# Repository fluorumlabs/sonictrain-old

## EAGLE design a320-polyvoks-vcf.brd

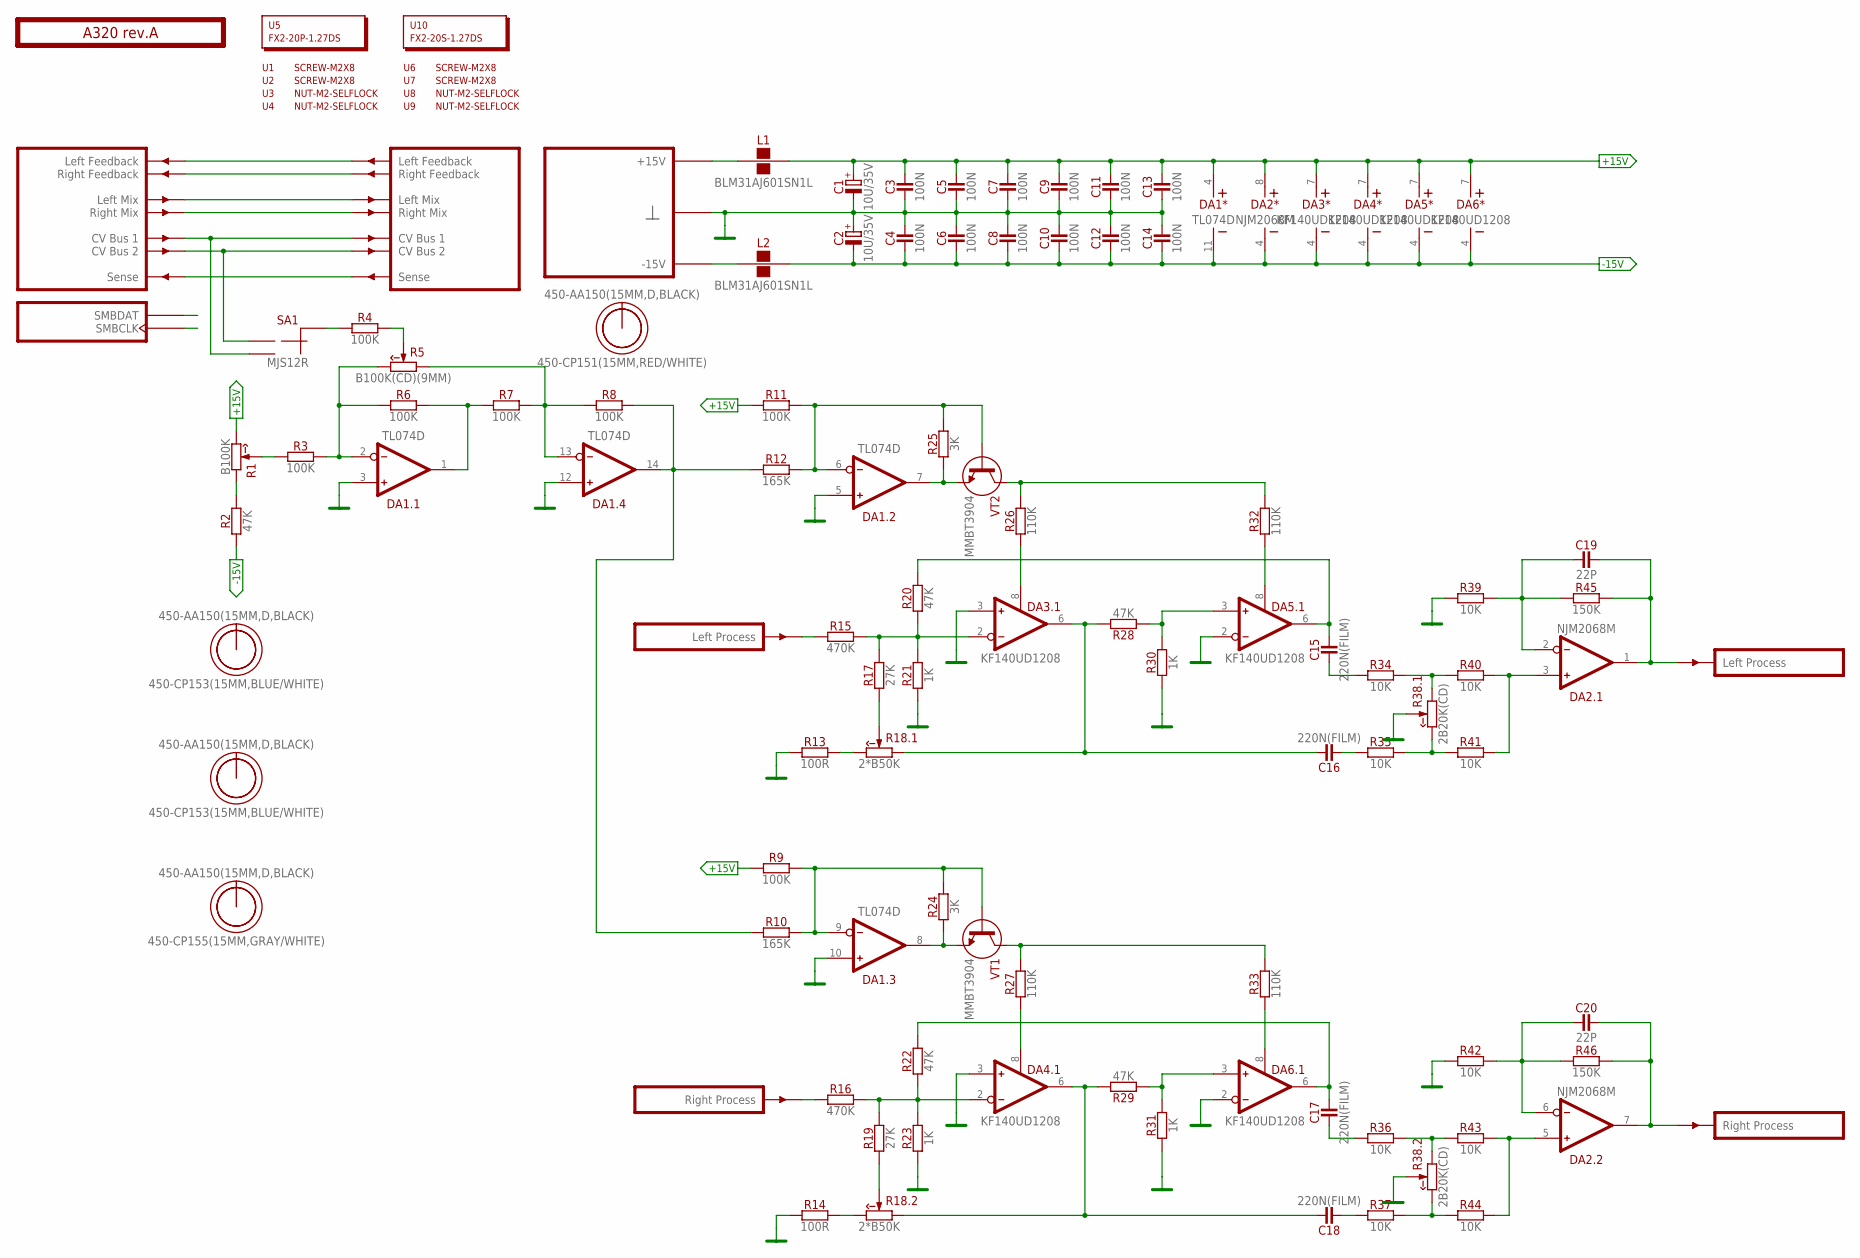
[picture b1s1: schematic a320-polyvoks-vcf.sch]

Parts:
C1, C2: 10U/35V; E2-5
C3, C4, C5, C6, C7, C8, C9, C10, C11, C12, C13, C14: 100N; C-0805
C15, C16, C17, C18: 220N(FILM); C050-025X075
C19, C20: 22P; C-0805
DA1: TL074D; SO-14
DA2: NJM2068M; SO-8
DA3, DA4, DA5, DA6: KF140UD1208; SO-8
L1, L2: BLM31AJ601SN1L; 1206
O1, O3, O5, O7: 450-AA150(15MM,D,BLACK); EMPTY
O2, O4: 450-CP153(15MM,BLUE/WHITE); EMPTY
O6: 450-CP155(15MM,GRAY/WHITE); EMPTY
O8: 450-CP151(15MM,RED/WHITE); EMPTY
PCB1: A320 rev.A; ST2-BOARD-50
R1: B100K; RV11-SINGLE
R2, R20, R22, R28, R29: 47K; R-0805
R3, R4, R6, R7, R8, R9, R11: 100K; R-0805
R5: B100K(CD)(9MM); RV09-SINGLE
R10, R12: 165K; R-0805
R13, R14: 100R; R-0805
R15, R16: 470K; R-0805
R17, R19: 27K; R-0805
R18: 2*B50K; RV11-DUAL
R21, R23, R30, R31: 1K; R-0805
R24, R25: 3K; R-0805
R26, R27, R32, R33: 110K; R-0805
R34, R35, R36, R37, R39, R40, R41, R42, R43, R44: 10K; R-0805
R38: 2B20K(CD); RV11-DUAL
R45, R46: 150K; R-0805
SA1: MJS12R; APEM-MJS12R
U1, U2, U6, U7: SCREW-M2X8; EMPTY
U3, U4, U8, U9: NUT-M2-SELFLOCK; EMPTY
U5: FX2-20P-1.27DS; EMPTY
U10: FX2-20S-1.27DS; EMPTY
VT1, VT2: MMBT3904; SOT23

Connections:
+15V: C1.+, C3.2, C5.2, C7.2, C9.2, C11.2, C13.2, DA1.4 (V+), DA2.8 (V+), DA3.7 (V+), DA4.7 (V+), DA5.7 (V+), DA6.7 (V+), L1.2, R1.3 (CW), R9.1, R11.1
-15V: C2.-, C4.1, C6.1, C8.1, C10.1, C12.1, C14.1, DA1.11 (V-), DA2.4 (V-), DA3.4 (V-), DA4.4 (V-), DA5.4 (V-), DA6.4 (V-), L2.2, R2.1
GND: C1.-, C2.+, C3.1, C4.2, C5.1, C6.2, C7.1, C8.2, C9.1, C10.2, C11.1, C12.2, C13.1, C14.2, DA1.3 (IN+), DA1.5 (IN+), DA1.10 (IN+), DA1.12 (IN+), DA3.3 (IN+), DA4.3 (IN+), DA5.2 (IN-), DA6.2 (IN-), PCB1.B4 (GND), PCB1.B4' (GND), PCB1.B5 (GND), PCB1.B5' (GND), PCB1.B6 (GND), PCB1.B6' (GND), PCB1.B7 (GND), PCB1.B7' (GND), PCB1.B8 (GND), PCB1.B8' (GND), R13.1, R14.1, R21.1, R23.1, R30.1, R31.1, R38.2 (W), R38.2' (W), R39.1, R42.1
LMIX: PCB1.ALMIX (LMIX), PCB1.ALMIX' (LMIX')
unnamed: L1.1, PCB1.A+15 (P+15V), PCB1.A+15' (P+15V), PCB1.B+15 (P+15V), PCB1.B+15' (P+15V)
unnamed: PCB1.ALFBK (LFBK), PCB1.ALFBK' (LFBK')
unnamed: R4.2, R5.2 (W)
unnamed: PCB1.ARFBK (RFBK), PCB1.ARFBK' (RFBK')
unnamed: DA1.2 (IN-), R3.2, R5.3 (CW), R6.1
unnamed: DA1.1 (OUT), R6.2, R7.1
unnamed: DA1.13 (IN-), R5.1 (CCW), R7.2, R8.1
unnamed: R1.1 (CCW), R2.2
unnamed: R4.1, SA1.C (CM)
unnamed: R34.2, R38.1 (CCW), R40.1
unnamed: DA1.9 (IN-), R9.2, R10.2, R24.2, VT1.1 (B)
unnamed: DA1.6 (IN-), R11.2, R12.2, R25.2, VT2.1 (B)
unnamed: R1.2 (W), R3.1
unnamed: DA1.8 (OUT), R24.1, VT1.2 (E)
unnamed: PCB1.ACV1 (CV1), PCB1.ACV1' (CV1'), SA1.NO (2)
unnamed: PCB1.BSENSE (SENSE), PCB1.BSENSE' (SENSE')
unnamed: DA1.7 (OUT), R25.1, VT2.2 (E)
unnamed: DA2.3 (IN+), R40.2, R41.2
unnamed: R36.2, R38.1' (CCW), R43.1
unnamed: C19.2, DA2.1 (OUT), PCB1.BOUTL' (OUTL), R45.2
unnamed: C20.1, DA2.6 (IN-), R42.2, R46.1
unnamed: DA3.2 (IN-), R15.2, R17.2, R20.1, R21.2
unnamed: C16.2, DA3.6 (OUT), R18.1 (CCW), R28.2
unnamed: DA5.3 (IN+), R28.1, R30.2
unnamed: L2.1, PCB1.A-15 (P-15V), PCB1.A-15' (P-15V), PCB1.B-15 (P-15V), PCB1.B-15' (P-15V)
unnamed: DA3.8 (ISET), R26.1
unnamed: C15.2, DA5.6 (OUT), R20.2
unnamed: DA1.14 (OUT), R8.2, R10.1, R12.1
unnamed: R13.2, R18.3 (CW)
unnamed: R17.1, R18.2 (W)
unnamed: DA5.8 (ISET), R32.1
unnamed: R26.2, R32.2, VT2.3 (C)
unnamed: C15.1, R34.1
unnamed: C16.1, R35.1
unnamed: DA2.5 (IN+), R43.2, R44.2
unnamed: R37.2, R38.3' (CW), R44.1
unnamed: C20.2, DA2.7 (OUT), PCB1.BOUTR' (OUTR), R46.2
unnamed: PCB1.ASMBDAT (SMBDAT), PCB1.ASMBDAT' (SMBDAT)
unnamed: DA4.2 (IN-), R16.2, R19.2, R22.1, R23.2
unnamed: C18.2, DA4.6 (OUT), R18.1' (CCW), R29.2
unnamed: DA6.3 (IN+), R29.1, R31.2
unnamed: PCB1.ACV2 (CV2), PCB1.ACV2' (CV2'), SA1.NC (1)
unnamed: PCB1.ASMBCLK (SMBCLK), PCB1.ASMBCLK' (SMBCLK)
unnamed: C17.2, DA6.6 (OUT), R22.2
unnamed: R14.2, R18.3' (CW)
unnamed: R18.2' (W), R19.1
unnamed: DA4.8 (ISET), R27.1
unnamed: DA6.8 (ISET), R33.1
unnamed: R27.2, R33.2, VT1.3 (C)
unnamed: R35.2, R38.3 (CW), R41.1
unnamed: C17.1, R36.1
unnamed: C18.1, R37.1
unnamed: PCB1.BINL (INL), R15.1
unnamed: PCB1.BINR (INR), R16.1
unnamed: C19.1, DA2.2 (IN-), R39.2, R45.1
RMIX: PCB1.ARMIX (RMIX), PCB1.ARMIX' (RMIX')

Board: 2 copper layers, 96 parts (0 on the bottom side), 60 nets, no tracks yet.

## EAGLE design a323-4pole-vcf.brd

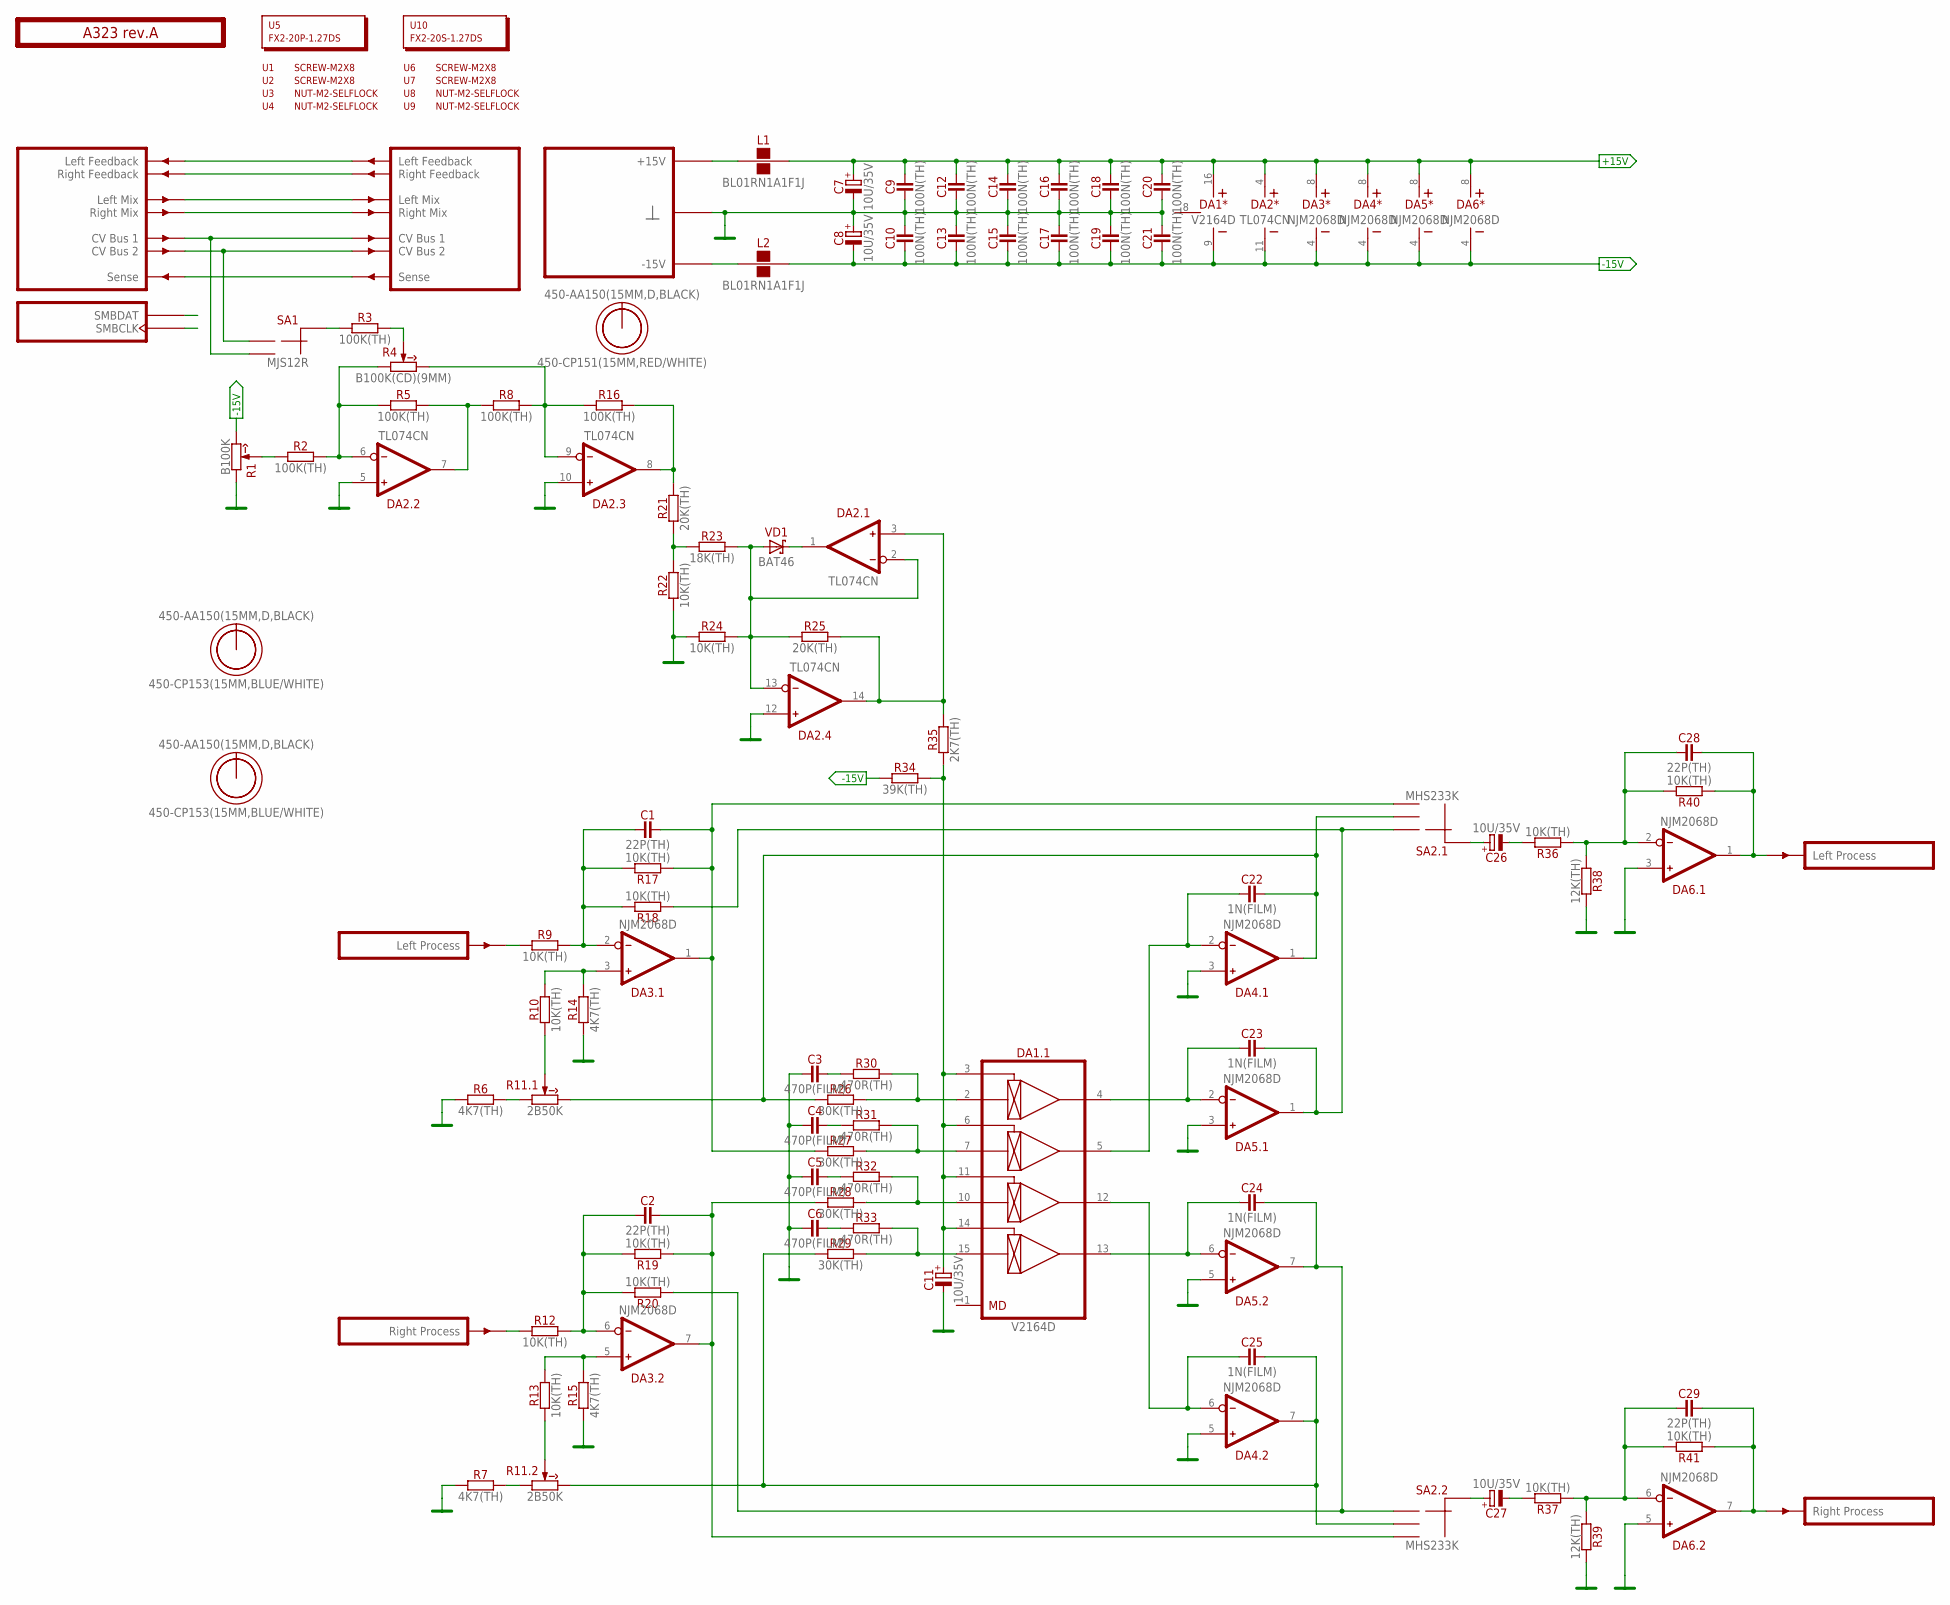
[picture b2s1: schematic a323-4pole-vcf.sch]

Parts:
C1, C2, C28, C29: 22P(TH); C050-024X044
C3, C4, C5, C6: 470P(FILM); C050-055X075
C7, C8, C11, C26, C27: 10U/35V; E2-5
C9, C10, C12, C13, C14, C15, C16, C17, C18, C19, C20, C21: 100N(TH); C050-024X044
C22, C23, C24, C25: 1N(FILM); C050-025X075
DA1: V2164D; DIP-16
DA2: TL074CN; DIP-14
DA3, DA4, DA5, DA6: NJM2068D; DIP-8
L1, L2: BL01RN1A1F1J; BL01RN1A
O1, O3, O5: 450-AA150(15MM,D,BLACK); EMPTY
O2, O4: 450-CP153(15MM,BLUE/WHITE); EMPTY
O6: 450-CP151(15MM,RED/WHITE); EMPTY
PCB1: A323 rev.A; ST2-BOARD-74
R1: B100K; RV11-SINGLE
R2, R3, R5, R8, R16: 100K(TH); R-0207/10
R4: B100K(CD)(9MM); RV09-SINGLE
R6, R7, R14, R15: 4K7(TH); R-0207/10
R9, R10, R12, R13, R17, R18, R19, R20, R22, R24, R36, R37, R40, R41: 10K(TH); R-0207/10
R11: 2B50K; RV11-DUAL
R21, R25: 20K(TH); R-0207/10
R23: 18K(TH); R-0207/10
R26, R27, R28, R29: 30K(TH); R-0207/10
R30, R31, R32, R33: 470R(TH); R-0207/10
R34: 39K(TH); R-0207/10
R35: 2K7(TH); R-0207/10
R38, R39: 12K(TH); R-0207/10
SA1: MJS12R; APEM-MJS12R
SA2: MHS233K; APEM-MHS233K
U1, U2, U6, U7: SCREW-M2X8; EMPTY
U3, U4, U8, U9: NUT-M2-SELFLOCK; EMPTY
U5: FX2-20P-1.27DS; EMPTY
U10: FX2-20S-1.27DS; EMPTY
VD1: BAT46; DO35-7

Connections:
+15V: C7.+, C9.2, C12.2, C14.2, C16.2, C18.2, C20.2, DA1.16 (V+), DA2.4 (V+), DA3.8 (V+), DA4.8 (V+), DA5.8 (V+), DA6.8 (V+), L1.2
-15V: C8.-, C10.1, C13.1, C15.1, C17.1, C19.1, C21.1, DA1.9 (V-), DA2.11 (V-), DA3.4 (V-), DA4.4 (V-), DA5.4 (V-), DA6.4 (V-), L2.2, R1.3 (CW), R34.1
GND: C3.1, C4.1, C5.1, C6.1, C7.-, C8.+, C9.1, C10.2, C11.-, C12.1, C13.2, C14.1, C15.2, C16.1, C17.2, C18.1, C19.2, C20.1, C21.2, DA1.8 (GND), DA2.5 (IN+), DA2.10 (IN+), DA2.12 (IN+), DA4.3 (IN+), DA4.5 (IN+), DA5.3 (IN+), DA5.5 (IN+), DA6.3 (IN+), DA6.5 (IN+), PCB1.B4 (GND), PCB1.B4' (GND), PCB1.B5 (GND), PCB1.B5' (GND), PCB1.B6 (GND), PCB1.B6' (GND), PCB1.B7 (GND), PCB1.B7' (GND), PCB1.B8 (GND), PCB1.B8' (GND), R1.1 (CCW), R6.2, R7.2, R14.1, R15.1, R22.1, R24.1, R38.2, R39.2
LMIX: PCB1.ALMIX (LMIX), PCB1.ALMIX' (LMIX')
unnamed: L1.1, PCB1.A+15 (P+15V), PCB1.A+15' (P+15V), PCB1.B+15 (P+15V), PCB1.B+15' (P+15V)
unnamed: PCB1.ALFBK (LFBK), PCB1.ALFBK' (LFBK')
unnamed: R3.2, R4.2 (W)
unnamed: PCB1.ARFBK (RFBK), PCB1.ARFBK' (RFBK')
unnamed: DA2.6 (IN-), R2.2, R4.1 (CCW), R5.1
unnamed: DA2.7 (OUT), R5.2, R8.1
unnamed: DA2.9 (IN-), R4.3 (CW), R8.2, R16.1
unnamed: C2.1, DA3.6 (IN-), R12.2, R19.2, R20.2
unnamed: R3.1, SA1.C (CM)
unnamed: C1.1, DA3.2 (IN-), R9.2, R17.2, R18.2
unnamed: DA3.3 (IN+), R10.2, R14.2
unnamed: R10.1, R11.2 (W)
unnamed: R1.2 (W), R2.1
unnamed: R6.1, R11.1 (CCW)
unnamed: PCB1.ACV1 (CV1), PCB1.ACV1' (CV1'), SA1.NO (2)
unnamed: PCB1.BSENSE (SENSE), PCB1.BSENSE' (SENSE')
unnamed: R21.1, R22.2, R23.1
unnamed: DA1.2 (IN1), R26.2, R30.2
unnamed: C1.2, DA3.1 (OUT), R17.1, R27.1, SA2.3
unnamed: DA1.7 (IN2), R27.2, R31.2
unnamed: DA1.10 (IN3), R28.2, R32.2
unnamed: DA1.15 (IN4), R29.2, R33.2
unnamed: C3.2, R30.1
unnamed: C4.2, R31.1
unnamed: L2.1, PCB1.A-15 (P-15V), PCB1.A-15' (P-15V), PCB1.B-15 (P-15V), PCB1.B-15' (P-15V)
unnamed: C5.2, R32.1
unnamed: C6.2, R33.1
unnamed: DA2.8 (OUT), R16.2, R21.2
unnamed: DA3.5 (IN+), R13.2, R15.2
unnamed: R11.2' (W), R13.1
unnamed: R7.1, R11.1' (CCW)
unnamed: C26.+, SA2.CMN (CM)
unnamed: C2.2, DA3.7 (OUT), R19.1, R28.1, SA2.3' (3)
unnamed: C22.1, DA1.5 (OUT2), DA4.2 (IN-)
unnamed: C22.2, DA4.1 (OUT), R11.3 (CW), R26.1, SA2.2
unnamed: C23.1, DA1.4 (OUT1), DA5.2 (IN-)
unnamed: C23.2, DA5.1 (OUT), R18.1, SA2.1
unnamed: PCB1.ASMBDAT (SMBDAT), PCB1.ASMBDAT' (SMBDAT)
unnamed: C24.1, DA1.13 (OUT4), DA5.6 (IN-)
unnamed: C24.2, DA5.7 (OUT), R20.1, SA2.1' (1)
unnamed: C25.1, DA1.12 (OUT3), DA4.6 (IN-)
unnamed: PCB1.ACV2 (CV2), PCB1.ACV2' (CV2'), SA1.NC (1)
unnamed: PCB1.ASMBCLK (SMBCLK), PCB1.ASMBCLK' (SMBCLK)
unnamed: C25.2, DA4.7 (OUT), R11.3' (CW), R29.1, SA2.2' (2)
unnamed: C26.-, R36.2
unnamed: C28.1, DA6.2 (IN-), R36.1, R38.1, R40.2
unnamed: PCB1.BINL (INL), R9.1
unnamed: C28.2, DA6.1 (OUT), PCB1.BOUTL' (OUTL), R40.1
unnamed: C27.+, SA2.CMN' (CM)
unnamed: C27.-, R37.2
unnamed: C29.1, DA6.6 (IN-), R37.1, R39.1, R41.2
unnamed: C29.2, DA6.7 (OUT), PCB1.BOUTR' (OUTR), R41.1
unnamed: DA2.1 (OUT), VD1.C
unnamed: DA2.3 (IN+), DA2.14 (OUT), R25.2, R35.2
unnamed: DA2.2 (IN-), DA2.13 (IN-), R23.2, R24.2, R25.1, VD1.A
unnamed: PCB1.BINR (INR), R12.1
unnamed: C11.+, DA1.3 (CV1), DA1.6 (CV2), DA1.11 (CV3), DA1.14 (CV4), R34.2, R35.1
RMIX: PCB1.ARMIX (RMIX), PCB1.ARMIX' (RMIX')

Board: 2 copper layers, 98 parts (0 on the bottom side), 62 nets, no tracks yet.

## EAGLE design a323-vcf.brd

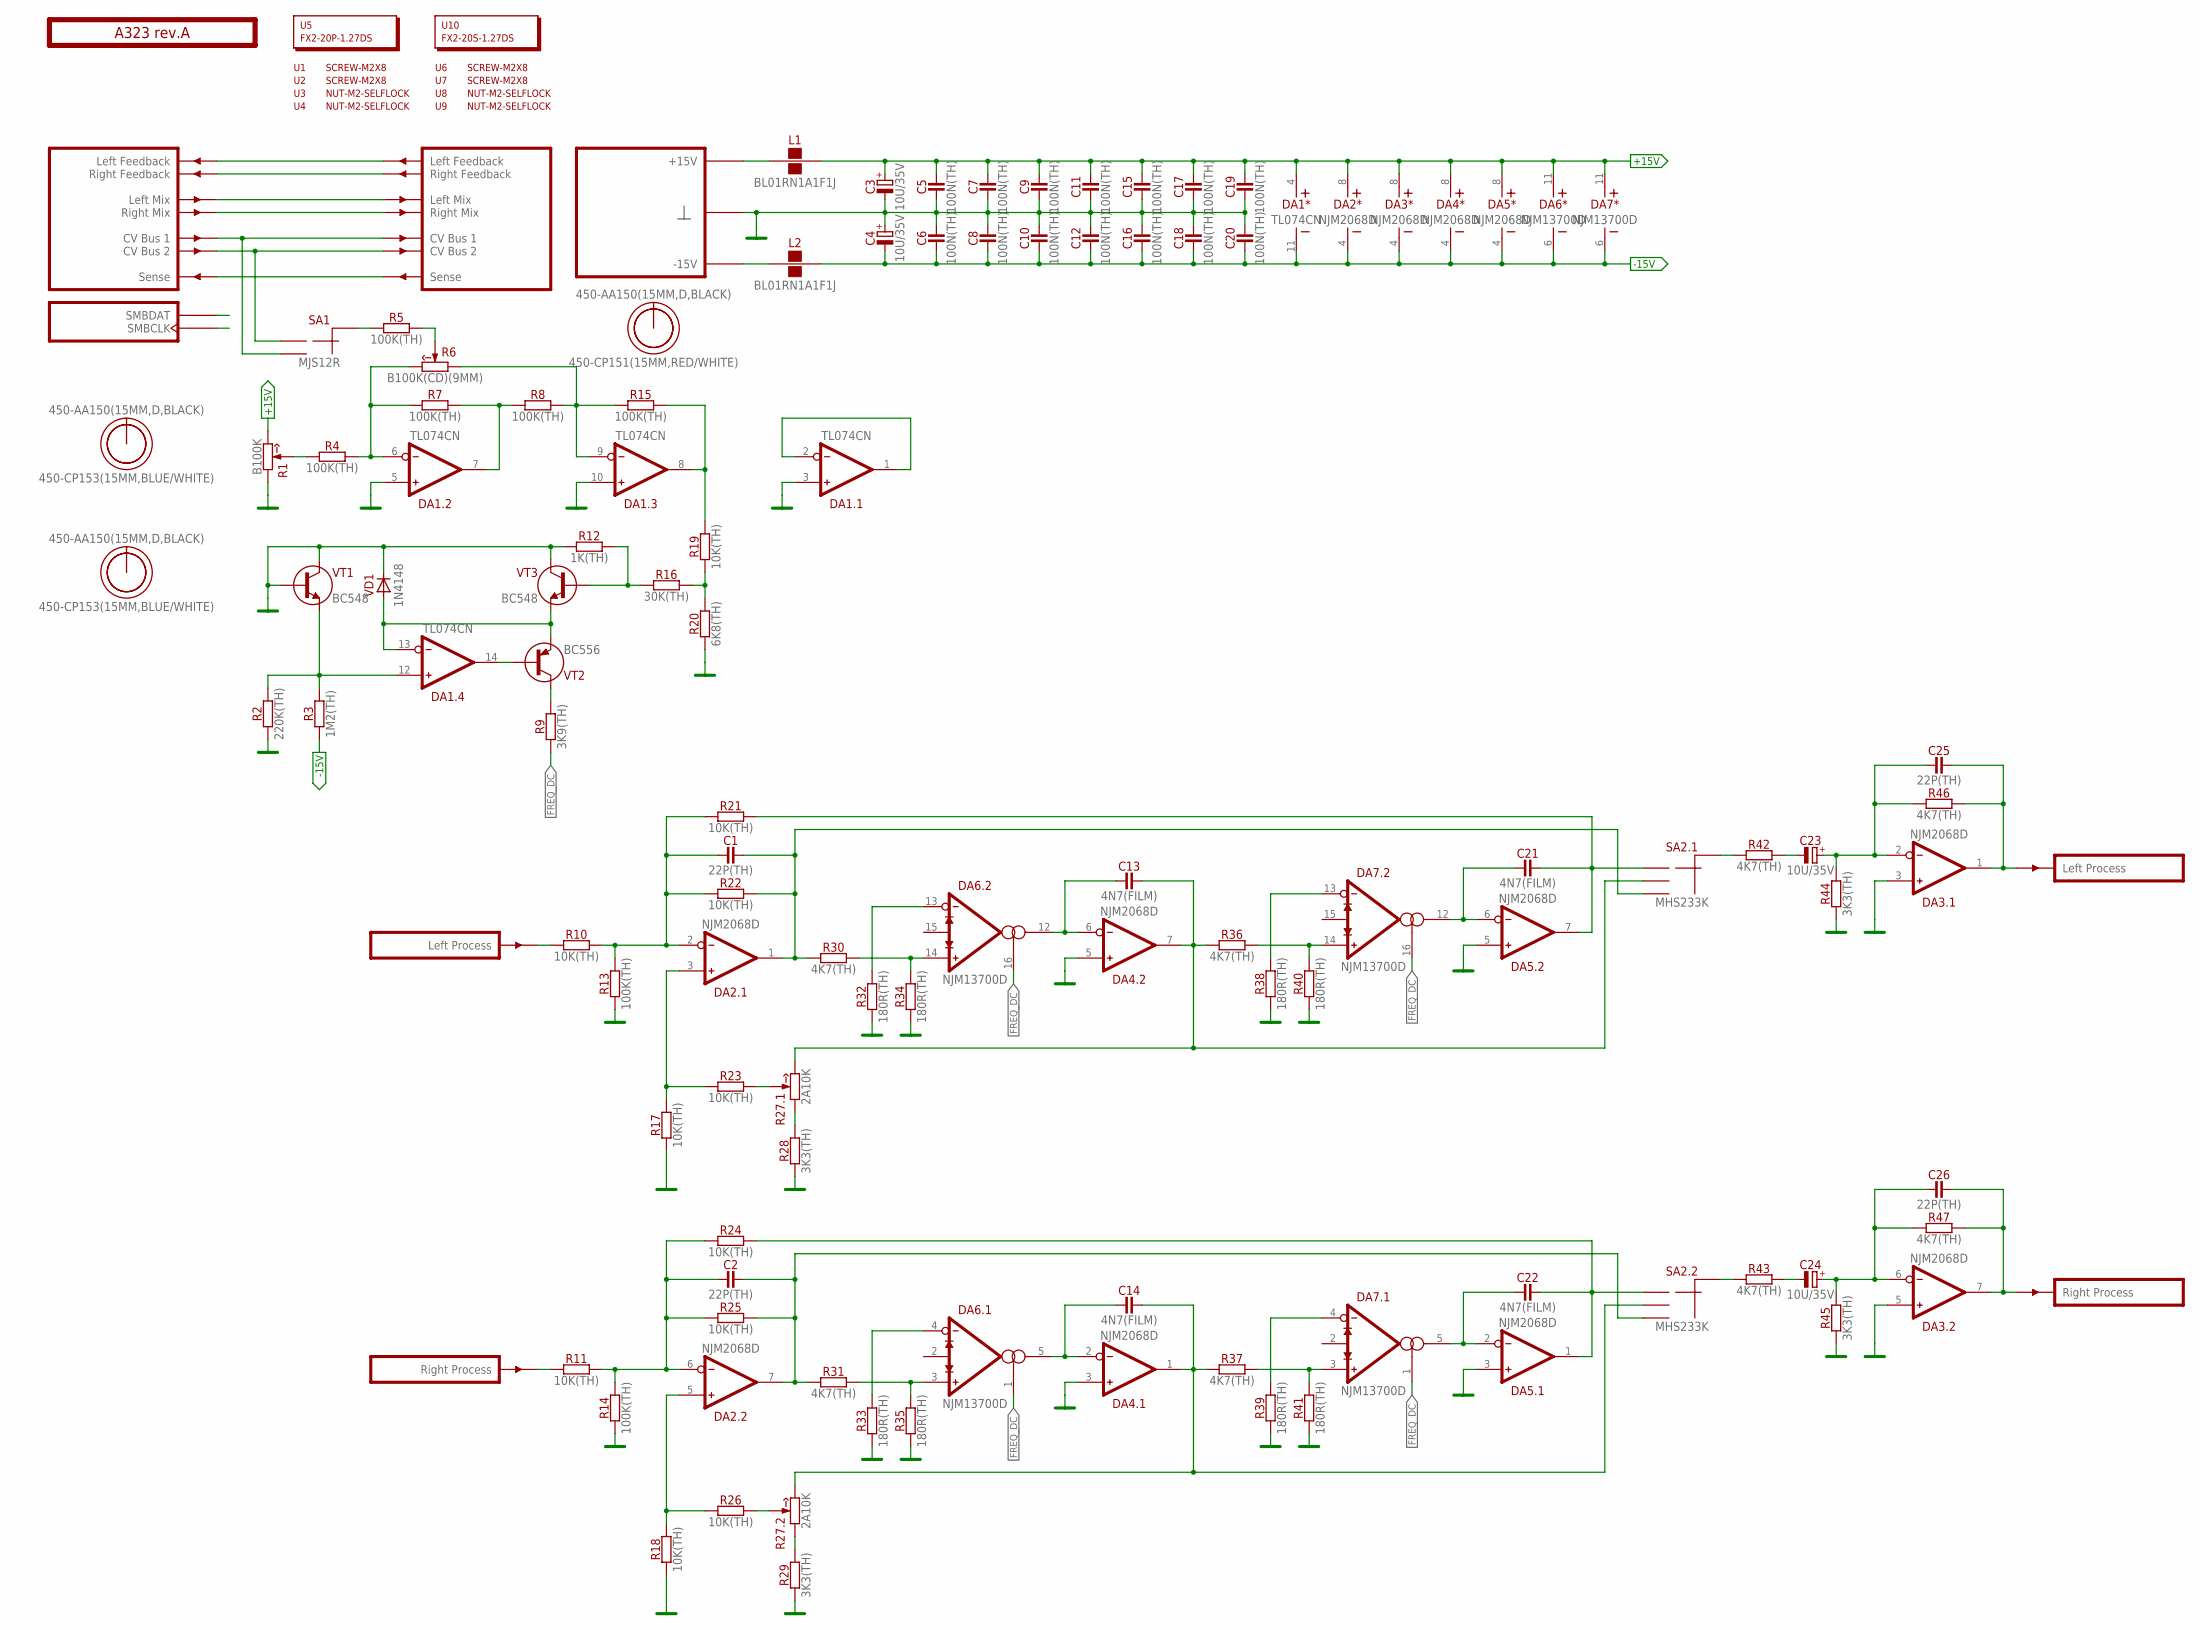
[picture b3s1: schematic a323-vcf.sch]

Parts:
C1, C2, C25, C26: 22P(TH); C050-024X044
C3, C4, C23, C24: 10U/35V; E2-5
C5, C6, C7, C8, C9, C10, C11, C12, C15, C16, C17, C18, C19, C20: 100N(TH); C050-024X044
C13, C14, C21, C22: 4N7(FILM); C050-025X075
DA1: TL074CN; DIP-14
DA2, DA3, DA4, DA5: NJM2068D; DIP-8
DA6, DA7: NJM13700D; DIP-16
L1, L2: BL01RN1A1F1J; BL01RN1A
O1, O3, O5: 450-AA150(15MM,D,BLACK); EMPTY
O2, O4: 450-CP153(15MM,BLUE/WHITE); EMPTY
O6: 450-CP151(15MM,RED/WHITE); EMPTY
PCB1: A323 rev.A; ST2-BOARD-74
R1: B100K; RV11-SINGLE
R2: 220K(TH); R-0207/10
R3: 1M2(TH); R-0207/10
R4, R5, R7, R8, R13, R14, R15: 100K(TH); R-0207/10
R6: B100K(CD)(9MM); RV09-SINGLE
R9: 3K9(TH); R-0207/10
R10, R11, R17, R18, R19, R21, R22, R23, R24, R25, R26: 10K(TH); R-0207/10
R12: 1K(TH); R-0207/10
R16: 30K(TH); R-0207/10
R20: 6K8(TH); R-0207/10
R27: 2A10K; RV11-DUAL
R28, R29, R44, R45: 3K3(TH); R-0207/10
R30, R31, R36, R37, R42, R43, R46, R47: 4K7(TH); R-0207/10
R32, R33, R34, R35, R38, R39, R40, R41: 180R(TH); R-0207/10
SA1: MJS12R; APEM-MJS12R
SA2: MHS233K; APEM-MHS233K
U1, U2, U6, U7: SCREW-M2X8; EMPTY
U3, U4, U8, U9: NUT-M2-SELFLOCK; EMPTY
U5: FX2-20P-1.27DS; EMPTY
U10: FX2-20S-1.27DS; EMPTY
VD1: 1N4148; DO35-7
VT1, VT3: BC548; TO92
VT2: BC556; TO92

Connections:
+15V: C3.+, C5.2, C7.2, C9.2, C11.2, C15.2, C17.2, C19.2, DA1.4 (V+), DA2.8 (V+), DA3.8 (V+), DA4.8 (V+), DA5.8 (V+), DA6.11 (V+), DA7.11 (V+), L1.2, R1.3 (CW)
-15V: C4.-, C6.1, C8.1, C10.1, C12.1, C16.1, C18.1, C20.1, DA1.11 (V-), DA2.4 (V-), DA3.4 (V-), DA4.4 (V-), DA5.4 (V-), DA6.6 (V-), DA7.6 (V-), L2.2, R3.1
FREQ_DC: DA6.1 (AMP_BIAS), DA6.16 (AMP_BIAS), DA7.1 (AMP_BIAS), DA7.16 (AMP_BIAS), R9.1
GND: C3.-, C4.+, C5.1, C6.2, C7.1, C8.2, C9.1, C10.2, C11.1, C12.2, C15.1, C16.2, C17.1, C18.2, C19.1, C20.2, DA1.3 (IN+), DA1.5 (IN+), DA1.10 (IN+), DA3.3 (IN+), DA3.5 (IN+), DA4.3 (IN+), DA4.5 (IN+), DA5.3 (IN+), DA5.5 (IN+), PCB1.B4 (GND), PCB1.B4' (GND), PCB1.B5 (GND), PCB1.B5' (GND), PCB1.B6 (GND), PCB1.B6' (GND), PCB1.B7 (GND), PCB1.B7' (GND), PCB1.B8 (GND), PCB1.B8' (GND), R1.1 (CCW), R2.1, R12.1, R13.1, R14.1, R17.1, R18.1, R20.1, R28.1, R29.1, R32.1, R33.1, R34.1, R35.1, R38.1, R39.1, R40.1, R41.1, R44.1, R45.1, VD1.C, VT1.1 (C), VT1.2 (B), VT3.1 (C)
LMIX: PCB1.ALMIX (LMIX), PCB1.ALMIX' (LMIX')
unnamed: L1.1, PCB1.A+15 (P+15V), PCB1.A+15' (P+15V), PCB1.B+15 (P+15V), PCB1.B+15' (P+15V)
unnamed: PCB1.ALFBK (LFBK), PCB1.ALFBK' (LFBK')
unnamed: R5.2, R6.2 (W)
unnamed: PCB1.ARFBK (RFBK), PCB1.ARFBK' (RFBK')
unnamed: DA1.6 (IN-), R4.2, R6.3 (CW), R7.1
unnamed: DA1.7 (OUT), R7.2, R8.1
unnamed: DA1.9 (IN-), R6.1 (CCW), R8.2, R15.1
unnamed: R16.2, R19.1, R20.2
unnamed: R5.1, SA1.C (CM)
unnamed: R12.2, R16.1, VT3.2 (B)
unnamed: R42.1, SA2.CMN (CM)
unnamed: C1.1, DA2.2 (IN-), R10.2, R13.2, R21.1, R22.1
unnamed: R1.2 (W), R4.1
unnamed: DA1.13 (IN-), VD1.A, VT2.3 (E), VT3.3 (E)
unnamed: PCB1.ACV1 (CV1), PCB1.ACV1' (CV1'), SA1.NO (2)
unnamed: PCB1.BSENSE (SENSE), PCB1.BSENSE' (SENSE')
unnamed: DA1.14 (OUT), VT2.2 (B)
unnamed: R9.2, VT2.1 (C)
unnamed: DA1.12 (IN+), R2.2, R3.2, VT1.3 (E)
unnamed: DA2.3 (IN+), R17.2, R23.1
unnamed: R23.2, R27.2 (W)
unnamed: R27.1 (CCW), R28.2
unnamed: C1.2, DA2.1 (OUT), R22.2, R30.1, SA2.3
unnamed: DA6.14 (IN+), R30.2, R34.2
unnamed: L2.1, PCB1.A-15 (P-15V), PCB1.A-15' (P-15V), PCB1.B-15 (P-15V), PCB1.B-15' (P-15V)
unnamed: DA6.13 (IN-), R32.2
unnamed: C13.1, DA4.6 (IN-), DA6.12 (OUT)
unnamed: DA1.8 (OUT), R15.2, R19.2
unnamed: C13.2, DA4.7 (OUT), R27.3 (CW), R36.1, SA2.2
unnamed: DA7.14 (IN+), R36.2, R40.2
unnamed: DA7.13 (IN-), R38.2
unnamed: C23.-, R42.2
unnamed: C21.1, DA5.6 (IN-), DA7.12 (OUT)
unnamed: C21.2, DA5.7 (OUT), R21.2, SA2.1
unnamed: C23.+, C25.1, DA3.2 (IN-), R44.2, R46.1
unnamed: C25.2, DA3.1 (OUT), PCB1.BOUTL' (OUTL), R46.2
unnamed: C2.1, DA2.6 (IN-), R11.2, R14.2, R24.1, R25.1
unnamed: PCB1.ASMBDAT (SMBDAT), PCB1.ASMBDAT' (SMBDAT)
unnamed: DA2.5 (IN+), R18.2, R26.1
unnamed: R26.2, R27.2' (W)
unnamed: R27.1' (CCW), R29.2
unnamed: PCB1.ACV2 (CV2), PCB1.ACV2' (CV2'), SA1.NC (1)
unnamed: PCB1.ASMBCLK (SMBCLK), PCB1.ASMBCLK' (SMBCLK)
unnamed: C2.2, DA2.7 (OUT), R25.2, R31.1, SA2.3' (3)
unnamed: DA6.3 (IN+), R31.2, R35.2
unnamed: DA6.4 (IN-), R33.2
unnamed: C14.1, DA4.2 (IN-), DA6.5 (OUT)
unnamed: C14.2, DA4.1 (OUT), R27.3' (CW), R37.1, SA2.2' (2)
unnamed: DA7.3 (IN+), R37.2, R41.2
unnamed: DA7.4 (IN-), R39.2
unnamed: C22.1, DA5.2 (IN-), DA7.5 (OUT)
unnamed: C22.2, DA5.1 (OUT), R24.2, SA2.1' (1)
unnamed: R43.1, SA2.CMN' (CM)
unnamed: C24.-, R43.2
unnamed: C24.+, C26.1, DA3.6 (IN-), R45.2, R47.1
unnamed: C26.2, DA3.7 (OUT), PCB1.BOUTR' (OUTR), R47.2
unnamed: PCB1.BINL (INL), R10.1
unnamed: PCB1.BINR (INR), R11.1
unnamed: DA1.1 (OUT), DA1.2 (IN-)
RMIX: PCB1.ARMIX (RMIX), PCB1.ARMIX' (RMIX')

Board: 2 copper layers, 105 parts (0 on the bottom side), 65 nets, no tracks yet.

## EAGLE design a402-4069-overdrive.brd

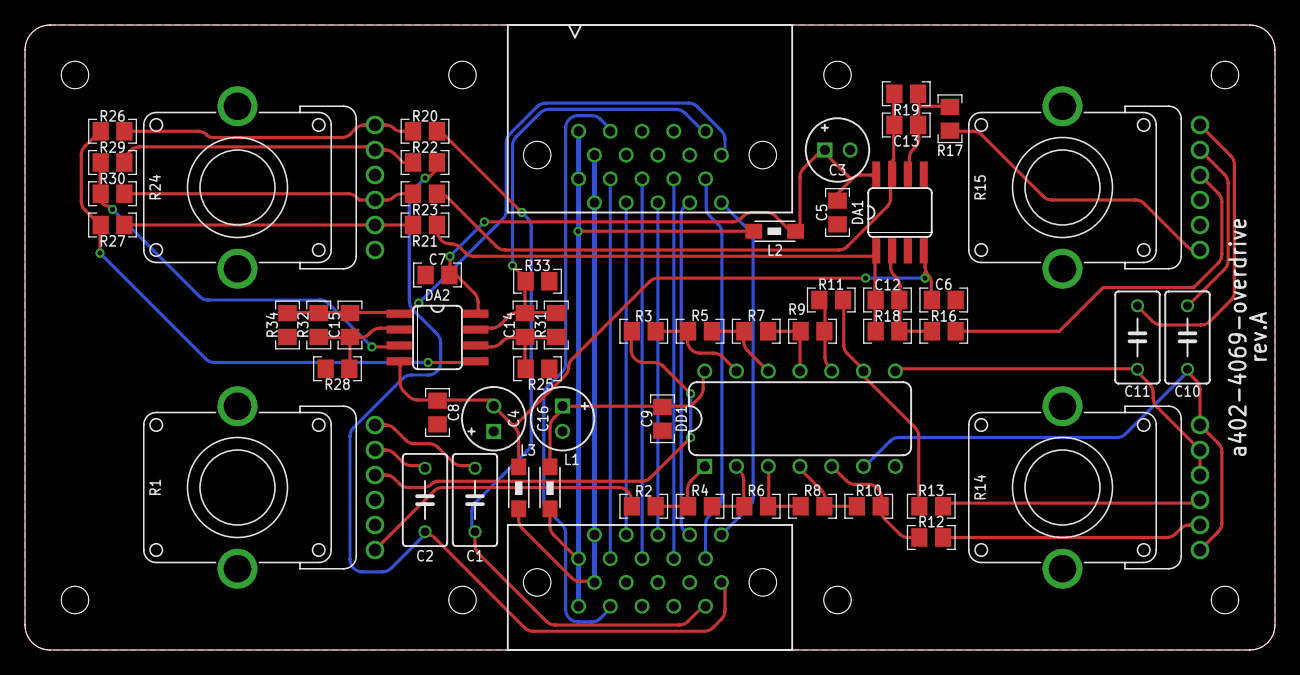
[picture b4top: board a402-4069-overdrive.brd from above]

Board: 2 copper layers, 100.0 x 50.0 mm, 68 parts (0 on the bottom side), 53 nets.

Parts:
C1, C2, C10, C11: 330N(FILM); C050-035X075
C3, C4, C16: 10U/35V; E2-5
C5, C6, C7, C8, C9: 100N; C-0805
C12, C13, C14, C15: 22P; C-0805
DA1, DA2: NJM2068M; SO-8
DD1: CD4069UBE; DIP-14
L1, L2, L3: BLM31AJ601SN1L; 1206
O1: EMPTY
O2, O4, O6, O8: 450-AA150(15MM,D,BLACK); EMPTY
O3, O7: 450-CP157(15MM,WHITE/BLACK); EMPTY
O5: 450-CP153(15MM,BLUE/WHITE); EMPTY
O9: 450-CP155(15MM,GRAY/WHITE); EMPTY
PCB1: rev.A; ST2-BOARD-50
R1, R15: 2*A10K; RV11-DUAL
R2, R3, R6, R7, R10, R11, R12, R13, R16, R17, R18, R19, R20, R21, R22, R23, R25, R26, R27, R28, R29, R30: 10K; R-0805
R4, R5, R8, R9, R33, R34: 100K; R-0805
R14: 2*A1M; RV11-DUAL
R24: 2*B20K(CD); RV11-DUAL
R31, R32: 15K; R-0805
U1: FX2-20P-1.27DS; EMPTY
U2: FX2-20S-1.27DS; EMPTY

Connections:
+15V: C3.+, C5.2, C7.2, DA1.8, DA2.8, L2.2
-15V: C4.-, C6.1, C8.1, DA1.4, DA2.4, L3.2
FBK_LEFT: PCB1.ALFBK, PCB1.ALFBK'
FBK_RIGHT: PCB1.ARFBK, PCB1.ARFBK'
GND: C3.-, C4.+, C5.1, C6.2, C7.1, C8.2, C9.1, C16.-, DA1.3, DA1.5, DD1.7, PCB1.B4, PCB1.B4', PCB1.B5, PCB1.B5', PCB1.B6, PCB1.B6', PCB1.B7, PCB1.B7', PCB1.B8, PCB1.B8', R1.1, R1.1', R15.1, R15.1', R24.2, R24.2', R25.1, R28.1, R33.2, R34.2
LMIX: PCB1.ALMIX, PCB1.ALMIX'
unnamed: C9.2, C16.+, DD1.14, L1.2
unnamed: R12.2, R14.1'
unnamed: R13.2, R14.1
unnamed: C1.2, PCB1.BINL, R20.1
unnamed: C1.1, R1.3'
unnamed: DD1.1, R2.1, R4.1
unnamed: DD1.2, R4.2, R6.1
unnamed: DD1.3, R6.2, R8.1
unnamed: DD1.4, R8.2, R10.1
unnamed: DD1.5, R10.2, R12.1
unnamed: C10.1, DD1.6, R14.2', R14.3'
unnamed: C10.2, R15.3
unnamed: R15.2, R16.1
unnamed: C12.1, DA1.2, R16.2, R18.1
unnamed: R1.2', R2.2
unnamed: PCB1.BSENSE, PCB1.BSENSE'
unnamed: C12.2, DA1.1, R18.2, R21.1
unnamed: C2.1, R1.3
unnamed: C2.2, PCB1.BINR, R22.1
unnamed: R1.2, R3.2
unnamed: DD1.13, R3.1, R5.1
unnamed: DD1.12, R5.2, R7.1
unnamed: DD1.11, R7.2, R9.1
unnamed: DD1.10, R9.2, R11.1
unnamed: DD1.9, R11.2, R13.1
unnamed: C11.1, DD1.8, R14.2, R14.3
unnamed: C14.2, DA2.7, PCB1.BOUTL', R31.2, R33.1
unnamed: C11.2, R15.3'
unnamed: R15.2', R17.1
unnamed: C13.1, DA1.6, R17.2, R19.1
unnamed: C13.2, DA1.7, R19.2, R23.1
unnamed: R20.2, R24.3', R26.1
unnamed: R22.2, R24.3, R29.1
unnamed: C15.1, DA2.2, R28.2, R32.1
unnamed: L3.1, PCB1.A-15, PCB1.A-15', PCB1.B-15, PCB1.B-15'
unnamed: C15.2, DA2.1, PCB1.BOUTR', R32.2, R34.1
unnamed: PCB1.ASMBDAT, PCB1.ASMBDAT'
unnamed: DA2.3, R29.2, R30.2
unnamed: R23.2, R24.1, R30.1
unnamed: PCB1.ACV1, PCB1.ACV1'
unnamed: PCB1.ACV2, PCB1.ACV2'
unnamed: PCB1.ASMBCLK, PCB1.ASMBCLK'
unnamed: DA2.5, R26.2, R27.2
unnamed: C14.1, DA2.6, R25.2, R31.1
unnamed: R21.2, R24.1', R27.1
P+15V: L1.1, L2.1, PCB1.A+15, PCB1.A+15', PCB1.B+15, PCB1.B+15'
RMIX: PCB1.ARMIX, PCB1.ARMIX'
